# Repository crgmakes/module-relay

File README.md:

# Relay Module

All the source files for the relay module hardware.

# Software 

You will need [KiCad](https://kicad.org) to view and edit this design. Click [here](https://www.kicad.org/download/) to download.

You will also need all the associated libraries and models to drive the design if you want to make changes or view the 3D rendering:

https://github.com/crgmakes/kicad-library.git

Kicad MUST be configured properly to use all the files in this repo. Once you have Kicad installed, under Preferences->Configure Paths..., make the following entries:

1 - KICAD_USER_DIR -> set to the root location of where you placed the above repository.
2 - KICAD_USER_LIBRARY = ${KICAD_USER_DIR}/Library
3 - KICAD_USER_MODEL_DIR = ${KICAD_USER_LIBRARY}/models
4 - KICAD_USER_TEMPLATE_DIR	= ${KICAD_USER_LIBRARY}/templates	

Kicad will operate mostly normally if these are not set properly. You will notice an issue when you view the PCB in 3D mode.

***NOTE***: after makeing a release build in git, if your rendered 3D images are missing components, ensure the path to EVERY component model is set to ${KICAD_USER_MODEL_DIR}/<model name>.

Kicad sometimes replaces the variable with an expansion and that FAILS during the build process because the expanded variable is local and does not match the build environment.

---

THE DESIGN IS PROVIDED "AS IS" AND THE AUTHOR DISCLAIMS ALL WARRANTIES WITH REGARD TO THIS DESIGN INCLUDING ALL IMPLIED WARRANTIES OF MERCHANTABILITY AND FITNESS. IN NO EVENT SHALL THE AUTHOR BE LIABLE FOR ANY SPECIAL, DIRECT, INDIRECT, OR CONSEQUENTIAL DAMAGES OR ANY DAMAGES WHATSOEVER RESULTING FROM LOSS OF USE, DATA OR PROFITS, WHETHER IN AN ACTION OF CONTRACT, NEGLIGENCE OR OTHER TORTIOUS ACTION, ARISING OUT OF OR IN CONNECTION WITH THE USE OR PERFORMANCE OF THIS DESIGN.

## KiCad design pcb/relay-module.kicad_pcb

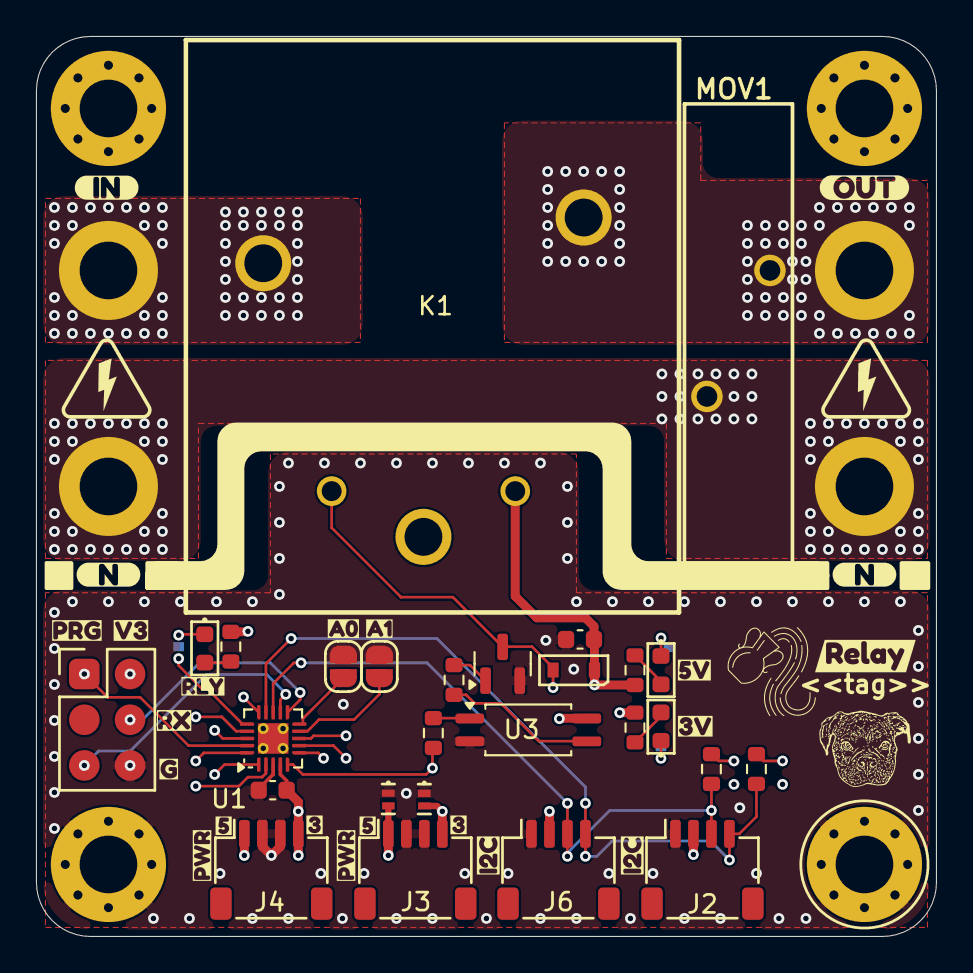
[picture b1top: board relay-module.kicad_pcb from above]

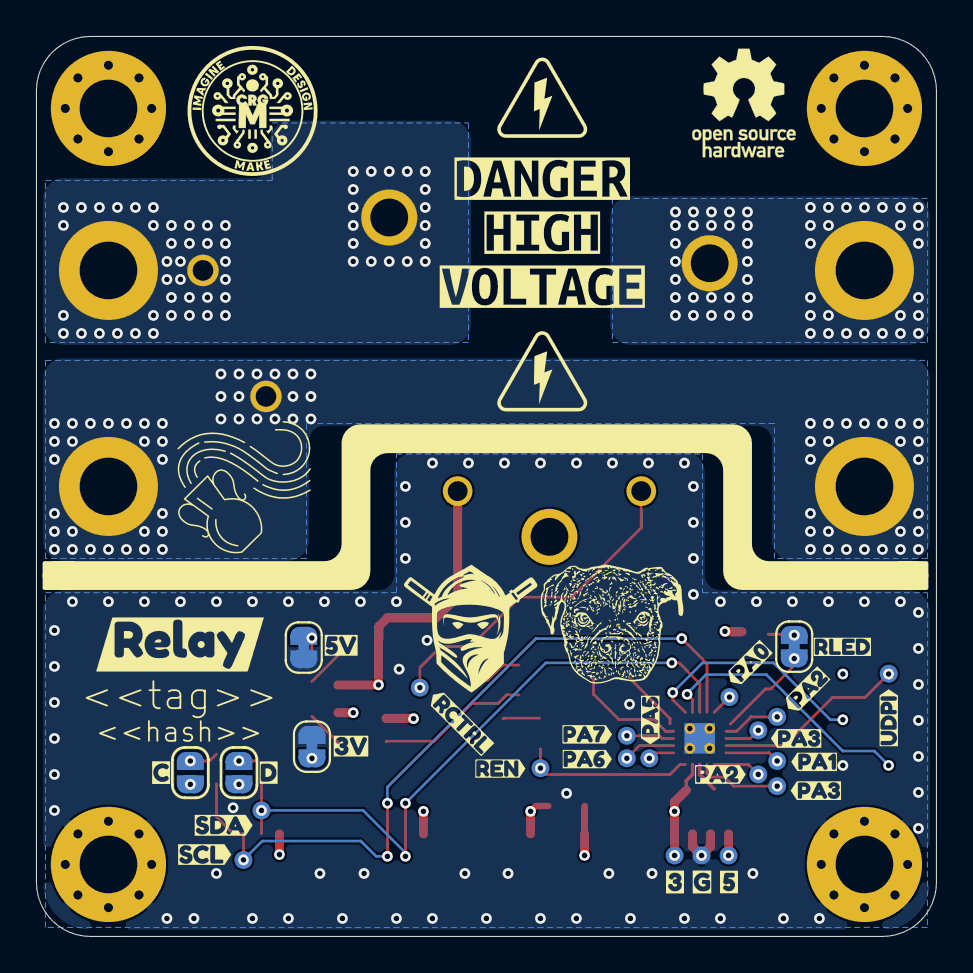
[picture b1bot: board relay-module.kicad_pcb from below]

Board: 4 copper layers, 50.0 x 50.0 mm, 116 parts (55 on the bottom side), 36 nets.

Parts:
C1, C2: 0.1uF; C_0603_1608Metric
D1: BAT48JFILM; SOD-323
D2, D3: Orange; LED_0603_1608Metric
D5: Red; LED_0603_1608Metric
D6: PESD5V5C1BL; DFN1006-2
D7: PESD3V3S1BL; DFN1006-2
H1, H2, H3, H4: MountingHole; MountingHole_3.2mm_M3_Pad_Via
J1: AVR-UPDI-UART-6; PinHeader_2x03_P2.54mm_Vertical_SMD
J2, J3, J4, J6: JST_SH_SM04B-SRSS-TB_1x04-1MP_P1.00mm_Horizontal
JP1, JP4, JP6: SolderJumper-2_P1.3mm_Bridged_RoundedPad1.0x1.5mm
JP2, JP3, JP7, JP8: SolderJumper-2_P1.3mm_Open_RoundedPad1.0x1.5mm
K1: PR24-5V-900-1A; RELAY_PR24-5V-900-1A
LOGO1: Aquarius Logo 8mm
LOGO2: CRGM Logo 7mm
LOGO3: Aquarius Logo 5mm
LOGO4: Roxy 5mm
LOGO5: OSHW-Logo_5.7x6mm_SilkScreen
LOGO6: Roxy 8mm
LOGO7: FNWW Face 8mm
MOV1: V250LA40BP
P1, P2, P3, P4: MountingHole_Pad; MountingHole_3.2mm_M3_ISO14580_Pad
Q1: MMBT3904; SOT-23
R1, R2: 220; R_0603_1608Metric
R3, R4, R12: 4.7K; R_0603_1608Metric
R7: 1k; R_0603_1608Metric
R15: 1K; R_0603_1608Metric
S1, S2, S3, S4: HIGH-VOLTAGE-5MM
TP1, TP2, TP3, TP6, TP7, TP8, TP9, TP10, TP11, TP12, TP13, TP14, TP15, TP16, TP20, TP21, TP22: TestPoint_Pad_D1.0mm
U1: ATtiny1616-MNR; VQFN-20-1EP_3x3mm_P0.4mm_EP1.7x1.7mm_ThermalVias
U3: TLP291; SOIC-4_4.55x2.6mm_P1.27mm
kibuzzard-67E371A7: G***; kibuzzard-67E371A7
kibuzzard-67E3720C, kibuzzard-67E3720C#2: G***; kibuzzard-67E3720C
kibuzzard-67E37192: G***; kibuzzard-67E37192
kibuzzard-68F5AC52: G***; kibuzzard-68F5AC52
kibuzzard-68F58F7A: G***; kibuzzard-68F58F7A
kibuzzard-68F58FDE: G***; kibuzzard-68F58FDE
kibuzzard-68F58FEF: G***; kibuzzard-68F58FEF
kibuzzard-68F595B8: G***; kibuzzard-68F595B8
kibuzzard-690A2BAF: G***; kibuzzard-690A2BAF
kibuzzard-690A2BB5: G***; kibuzzard-690A2BB5
kibuzzard-690A7DBB: G***; kibuzzard-690A7DBB
kibuzzard-690A7DC5: G***; kibuzzard-690A7DC5
kibuzzard-6918F9A4: G***; kibuzzard-6918F9A4
kibuzzard-6918FB8A: G***; kibuzzard-6918FB8A
kibuzzard-6918FB91: G***; kibuzzard-6918FB91
kibuzzard-69092EA7: G***; kibuzzard-69092EA7
kibuzzard-69092EAF: G***; kibuzzard-69092EAF
kibuzzard-69782BCF: G***; kibuzzard-69782BCF
kibuzzard-69782BD8: G***; kibuzzard-69782BD8
kibuzzard-690926DB: G***; kibuzzard-690926DB
kibuzzard-690932B6: G***; kibuzzard-690932B6
kibuzzard-690932D2: G***; kibuzzard-690932D2
kibuzzard-690932EF: G***; kibuzzard-690932EF
kibuzzard-690933B9: G***; kibuzzard-690933B9
kibuzzard-690933C6: G***; kibuzzard-690933C6
kibuzzard-690933D0: G***; kibuzzard-690933D0
kibuzzard-697827C3: G***; kibuzzard-697827C3
kibuzzard-697827D2: G***; kibuzzard-697827D2
kibuzzard-697827F7: G***; kibuzzard-697827F7
kibuzzard-697830E3, kibuzzard-697830E3#2: G***; kibuzzard-697830E3
kibuzzard-697831DA, kibuzzard-697831DA#2: G***; kibuzzard-697831DA
kibuzzard-6909280B: G***; kibuzzard-6909280B
kibuzzard-6978378C: G***; kibuzzard-6978378C
kibuzzard-69092782: G***; kibuzzard-69092782
kibuzzard-69092816: G***; kibuzzard-69092816
kibuzzard-69093282: G***; kibuzzard-69093282
kibuzzard-69093358: G***; kibuzzard-69093358
kibuzzard-69093373: G***; kibuzzard-69093373
kibuzzard-69093383: G***; kibuzzard-69093383
kibuzzard-69093389: G***; kibuzzard-69093389
kibuzzard-69093390: G***; kibuzzard-69093390
kibuzzard-69093403: G***; kibuzzard-69093403
kibuzzard-69179320: G***; kibuzzard-69179320
kibuzzard-69179327: G***; kibuzzard-69179327
kibuzzard-69179334: G***; kibuzzard-69179334

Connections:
+3.3V: C1.1, D7.2 (K2), J1.2 (VCC), J2.2, J3.4 (V3.3), J4.4 (V3.3), J6.2, JP7.2 (B), JP8.2 (B), R7.1, R15.1, TP21.1 (1_1), U1.4 (VCC), U3.4
+5V: C2.1, D1.1 (K), D6.2 (K2), J3.1 (V5), J4.1 (V5), K1.A1 (COIL1), R12.1, TP20.1 (1_1)
/MCU/A0: JP2.2 (B), U1.10 (PB4/0OUT)
/MCU/A1: JP3.2 (B), U1.9 (PB5/CLK0)
/MCU/PA1: TP8.1 (1_1), U1.20 (MOSI/PA1)
/MCU/PA2: TP9.1 (1_1), U1.1 (MISO/PA2)
/MCU/PA3: TP10.1 (1_1), U1.2 (SCK/PA3)
/MCU/PA5: TP12.1 (1_1), U1.6 (VREF/PA5)
/MCU/PA6: TP13.1 (1_1), U1.7 (DAC/PA6)
/MCU/PA7: TP14.1 (1_1), U1.8 (1OUT/PA7)
/MCU/PC0: TP11.1 (1_1), U1.15 (PC0/SCLK)
/MCU/PC2: TP6.1 (1_1), U1.17 (PC2)
/MCU/PC3: TP7.1 (1_1), U1.18 (PC3)
/Power/V3.3LED: D2.2 (A), R15.2
/Power/V5LED: D3.2 (A), R12.2
/Relay/LOAD_IN: K1.COM1, P3.1 (1_1)
/Relay/LOAD_OUT: K1.NO, MOV1.P$1, P4.1 (1_1)
/Relay/NEUTRAL: MOV1.P$2, P1.1 (1_1), P2.1 (1_1)
/Relay/RELAY_CTRL: D1.2 (A), K1.A2 (COIL2), Q1.3 (C), TP1.1 (1_1)
GND: C1.2, C2.2, D6.1 (K1), D7.1 (K1), H1.1 (1_1), H2.1 (1_1), J1.6 (GND), J2.1, J3.2 (GND), J3.3 (GND), J4.2 (GND), J4.3 (GND), J6.1, JP1.1 (A), JP2.1 (A), JP3.1 (A), JP4.1 (A), Q1.2 (E), TP22.1 (1_1), U1.3 (GND), U1.21 (GND), U3.2
unnamed: D2.1 (K), JP4.2 (B)
unnamed: D3.1 (K), JP1.2 (B)
unnamed: D5.2 (A), R7.2
unnamed: D5.1 (K), JP6.2 (B)
unnamed: JP7.1 (A), R4.2
unnamed: JP8.1 (A), R3.2
unnamed: Q1.1 (B), R2.2
unnamed: R1.2, U3.1
unnamed: R2.1, U3.3
RELAY_EN: R1.1, TP2.1 (1_1), U1.5 (~SS/PA4)
RELAY_LED: JP6.1 (A), U1.16 (PC1)
RXD: J1.4 (RXD), U1.11 (PB3/RxD)
SCL: J2.4, J6.4, R3.1, TP15.1 (1_1), U1.14 (PB0/SCL)
SDA: J2.3, J6.3, R4.1, TP16.1 (1_1), U1.13 (PB1/SDA)
TXD: J1.5 (TXD), U1.12 (PB2/TxD)
UPDI: J1.1 (DATA), TP3.1 (1_1), U1.19 (UPDI/PA0)

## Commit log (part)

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2025-03-26 Initial checking.
2025-03-26 initial checkin
2025-04-11 Updated silkscreen
2025-04-23 v1.0 Relay Module Panel 2x2
2025-04-23 removed unnecessary files.
2025-04-29 Updated for panelization.
2025-05-12 Added power, relay LEDs
2025-05-14 Changed 5v to orange LED
2025-06-09 Refined relay based testing
2025-06-12 Added CI files; deleted unnecessary files
2025-06-12 fixed upload to release error
2025-06-12 Fixed missing LCSC part numbers; updated CI script
2025-06-21 Rerouted after adding test points
    Added test points to all pins
    Added serial connector
    Added relay LED
    Changed symbols and footprints to CRGM
    Moved pins around to optimize routing
2025-06-21 schematic and PCB clean up
2025-06-21 Updated mounting holes; rounded corners
2025-06-22 Changed to multi-sheet
2025-06-26 Updated frame template
2025-06-27 Updated worksheet template
2025-06-27 Updated worksheet template and logo
2025-06-27 Updated CI script
2025-07-13 Update PCB layer colors and add requirements text box
    Specified silk screen and solder mask colors in relay-module.kicad_pcb and updated the 3D model path. Added a detailed PCB requirements text box to requirements.kicad_sch. Updated embedded image data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
2025-07-24 Updated license
2025-09-22 Fixed model path
2025-10-21 Updated to latest libraries
    Changed to all CRG footprints (mostly)
    Moved somethings around
    Added LED jumper
    Updated symbols/logos
2025-10-26 Updated .gitignore
2025-10-27 Fixed capacitor attributes
2025-11-03 Updated for consistency
    Updated footprints
    Added ESD to power
    Added second QWICC connector
    Rerouted as required
    Made mounting holes grounded
2025-11-04 Updated parts and models
2025-11-04 Fixed git scripts
2025-11-04 Updated panel options
    Hide symbol value
    Removed old 2x2 panel options
2025-11-05 Updated for DFM
2025-11-07 final clean up and processing
2025-11-16 Updated for DFM
    Updated board stack up - 2oz/1oz copper
    Move components around to add stitching vias
    Updated render in schematics
2025-11-17 Updated silkscreen, zones, and stitching vias
2025-12-28 Updated I2C pulls to open jumper
    Fixed I2C to be open rather than bridged.
    Changed opto-isolator to CRGM library.
    Updated picture of bottom side to match new footprint
2026-02-03 Updated for consistency with new patterns
2026-02-18 Silkscreen improvements
2026-03-01 replaced .wrl with .step
